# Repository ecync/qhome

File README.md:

# QHome Automation System

## 🏠 Project Overview
**QHome** is a comprehensive, full-stack IoT Smart Home solution designed to provide real-time monitoring, automation, and remote control of environmental and power sensors. The system is built on a modular architecture, spanning from custom PCB hardware design to a modern web-based dashboard.

This project integrates embedded systems connectivity (ESP32/ESP8266), robust backend services (NestJS/MQTT), and an interactive frontend (React) to create a seamless smart home experience.

## 🏗️ System Architecture

The system operates on a publish-subscribe model using MQTT for low-latency communication between the hardware nodes and the server.

```mermaid
graph LR
    subgraph Hardware Layer
        Node[ESP32 QHome Node]
        Sensors[Sensors: DHT, MQ, ACS, ZMPT]
        Relays[Relays & Actuators]
        Node --- Sensors
        Node --- Relays
    end

    subgraph Communication
        MQTT[MQTT Broker]
        WiFi[WiFi Network]
        Node -.->|MQTT/WS| WiFi
        WiFi -.-> MQTT
    end

    subgraph Cloud/Server Layer
        Backend[NestJS Backend]
        DB[(MongoDB)]
        Backend <-->|Pub/Sub| MQTT
        Backend <-->|Data Persistence| DB
    end

    subgraph User Interface
        Frontend[React Dashboard]
        User((User))
        User --> Frontend
        Frontend <-->|HTTP/REST| Backend
        Frontend <-->|Socket.io| Backend
    end
```

## 📊 Data Flow Diagram

This diagram illustrates how data moves through the entire system, from sensor acquisition to user visualization.

```mermaid
flowchart TB
    subgraph IoT_Node["IoT Node Layer"]
        Sensors[Physical Sensors<br/>DHT, MQ, ACS, ZMPT, PIR, LDR]
        ADC[Analog-to-Digital<br/>Conversion]
        Process[Data Processing<br/>& Aggregation]
        JSON[JSON Payload<br/>Generation]
        
        Sensors -->|Analog/Digital| ADC
        ADC -->|Raw Values| Process
        Process -->|Structured Data| JSON
    end
    
    subgraph Communication_Layer["Communication Layer"]
        WiFi[WiFi Module]
        MQTT_Pub[MQTT Publisher<br/>Topic: node/send]
        MQTT_Broker[MQTT Broker<br/>158.101.98.79:9001]
        MQTT_Sub[MQTT Subscriber<br/>Topic: node/cmd]
        
        JSON -->|Transmit| WiFi
        WiFi -->|Publish| MQTT_Pub
        MQTT_Pub -->|WebSocket| MQTT_Broker
        MQTT_Broker -->|Commands| MQTT_Sub
        MQTT_Sub -->|Receive| WiFi
    end
    
    subgraph Backend_Layer["Backend Service Layer"]
        Gateway[MQTT Gateway<br/>Service]
        Validator[Data Validator<br/>& Parser]
        EventEmitter[Event Emitter]
        DB_Write[Database Writer]
        Socket_Emit[Socket.IO Emitter]
        MongoDB[(MongoDB<br/>Collections)]
        API[REST API<br/>Controllers]
        
        MQTT_Broker -->|Subscribed Data| Gateway
        Gateway -->|Validate| Validator
        Validator -->|Emit Events| EventEmitter
        EventEmitter -->|Store| DB_Write
        EventEmitter -->|Broadcast| Socket_Emit
        DB_Write -->|Persist| MongoDB
        API -->|Query| MongoDB
    end
    
    subgraph Frontend_Layer["Frontend Application Layer"]
        Socket_Client[Socket.IO Client]
        State[React State<br/>Management]
        UI_Dashboard[Dashboard UI<br/>Components]
        UI_Analytics[Analytics UI<br/>Charts]
        HTTP_Client[HTTP Client<br/>API Service]
        
        Socket_Emit -.->|Real-time Push| Socket_Client
        Socket_Client -->|Update| State
        HTTP_Client -->|Fetch Historical| API
        API -->|Response| HTTP_Client
        HTTP_Client -->|Update| State
        State -->|Render| UI_Dashboard
        State -->|Render| UI_Analytics
    end
    
    subgraph User_Layer["User Interaction"]
        User((User))
        Browser[Web Browser]
        
        User -->|View/Control| Browser
        Browser <-->|Display| UI_Dashboard
        Browser <-->|Display| UI_Analytics
        Browser -->|Commands| HTTP_Client
    end
    
    HTTP_Client -.->|Control Commands| API
    API -.->|Publish to node/cmd| MQTT_Broker
    
    style IoT_Node fill:#e1f5ff
    style Communication_Layer fill:#fff3e0
    style Backend_Layer fill:#f3e5f5
    style Frontend_Layer fill:#e8f5e9
    style User_Layer fill:#fce4ec
```

### Data Flow Description

**1. Sensor Data Acquisition (IoT Node)**
- Physical sensors continuously monitor environmental and power parameters
- Analog sensors output voltage levels converted to digital values via ADC
- Data is processed, calibrated, and packaged into JSON format

**2. Data Transmission (Communication Layer)**
- JSON payload transmitted over WiFi to MQTT broker
- Published to `node/send` topic via WebSocket protocol
- Bidirectional communication allows receiving commands on `node/cmd` topic

**3. Data Processing (Backend Service)**
- MQTT Gateway subscribes to node data streams
- Incoming data is validated and parsed
- Event system triggers parallel operations:
  - Persistent storage in MongoDB collections
  - Real-time broadcast to connected frontend clients via Socket.IO

**4. Data Presentation (Frontend Application)**
- Socket.IO client receives real-time updates for live dashboard
- HTTP client fetches historical data for analytics and trends
- React state management updates UI components reactively

**5. User Control Loop**
- User interactions trigger API calls to backend
- Backend publishes control commands to MQTT broker
- IoT node receives and executes commands (relay control, configuration updates)

## 🔄 Software Flow Diagram

This diagram shows the complete software execution flow from system startup to continuous operation.

```mermaid
flowchart TD
    Start([System Power On]) --> Init_Check{Component<br/>Ready?}
    
    Init_Check -->|Hardware| Init_Hardware[Initialize Hardware<br/>• GPIO Pins<br/>• LCD Display<br/>• Sensors<br/>• Relays]
    Init_Check -->|Backend| Init_Backend[Initialize Backend<br/>• Load Config<br/>• Connect MongoDB<br/>• Start HTTP Server]
    Init_Check -->|Frontend| Init_Frontend[Initialize Frontend<br/>• Load React App<br/>• Check Session<br/>• Setup Routes]
    
    Init_Hardware --> Check_Config{Config<br/>Exists?}
    Check_Config -->|No| AP_Mode[Start WiFi AP Mode<br/>Show Config Portal]
    AP_Mode --> Wait_Config[Wait for User<br/>to Configure WiFi]
    Wait_Config -->|Configured| Save_Config[Save to EEPROM]
    Save_Config --> Connect_WiFi
    
    Check_Config -->|Yes| Connect_WiFi[Connect to WiFi]
    Connect_WiFi --> WiFi_Success{Connected?}
    WiFi_Success -->|No| AP_Mode
    WiFi_Success -->|Yes| Connect_MQTT[Connect to<br/>MQTT Broker]
    
    Connect_MQTT --> MQTT_Success{Connected?}
    MQTT_Success -->|No| Retry_MQTT[Retry Connection<br/>Exponential Backoff]
    Retry_MQTT --> MQTT_Success
    MQTT_Success -->|Yes| Subscribe_Topics[Subscribe to<br/>node/cmd Topic]
    
    Init_Backend --> Connect_DB[Connect to MongoDB]
    Connect_DB --> DB_Success{Connected?}
    DB_Success -->|No| Error_Exit[Log Error & Exit]
    DB_Success -->|Yes| Connect_MQTT_Backend[Connect to<br/>MQTT Broker as Client]
    Connect_MQTT_Backend --> Backend_Subscribe[Subscribe to<br/>node/send Topic]
    Backend_Subscribe --> Start_API[Start REST API<br/>& Socket.IO Server]
    
    Init_Frontend --> Check_Auth{User<br/>Authenticated?}
    Check_Auth -->|No| Show_Login[Show Login Page]
    Show_Login --> User_Login[User Enters<br/>Credentials]
    User_Login --> Validate_Auth[Validate Against<br/>Backend API]
    Validate_Auth --> Auth_Valid{Valid?}
    Auth_Valid -->|No| Show_Login
    Auth_Valid -->|Yes| Store_Session[Store Session<br/>in SessionStorage]
    
    Check_Auth -->|Yes| Load_Dashboard
    Store_Session --> Load_Dashboard[Load Dashboard<br/>Components]
    Load_Dashboard --> Connect_Socket[Connect Socket.IO<br/>to Backend]
    
    Subscribe_Topics --> Ready_Node[Node Ready<br/>Play Beep Sound]
    Start_API --> Ready_Backend[Backend Ready<br/>Log Status]
    Connect_Socket --> Ready_Frontend[Frontend Ready<br/>Display Dashboard]
    
    Ready_Node --> Main_Loop_Node[Main Loop: Node]
    Ready_Backend --> Main_Loop_Backend[Main Loop: Backend]
    Ready_Frontend --> Main_Loop_Frontend[Main Loop: Frontend]
    
    Main_Loop_Node --> Read_Sensors[Read All Sensors<br/>Every Interval]
    Read_Sensors --> Process_Data[Process & Calculate<br/>• Temperature/Humidity<br/>• Gas Level<br/>• Power/Energy<br/>• Motion/Light]
    Process_Data --> Check_Thresholds{Thresholds<br/>Exceeded?}
    Check_Thresholds -->|Yes| Trigger_Alert[Trigger Local Alert<br/>• Activate Buzzer<br/>• Update LCD<br/>• Send MQTT Alert]
    Check_Thresholds -->|No| Check_Sync
    Trigger_Alert --> Check_Sync
    
    Check_Sync{Time to<br/>Sync?} -->|Yes| Publish_Data[Publish JSON<br/>to node/send]
    Check_Sync -->|No| Update_Display
    Publish_Data --> Update_Display[Update LCD<br/>Display Status]
    
    Update_Display --> Listen_Commands[Listen for<br/>MQTT Commands]
    Listen_Commands --> Command_Received{Command?}
    Command_Received -->|Yes| Execute_Command[Execute Command<br/>• Toggle Relay<br/>• Update Config<br/>• Restart]
    Command_Received -->|No| Main_Loop_Node
    Execute_Command --> Main_Loop_Node
    
    Main_Loop_Backend --> Listen_MQTT[Listen for<br/>MQTT Messages]
    Listen_MQTT --> MQTT_Message{Message<br/>Received?}
    MQTT_Message -->|Yes| Parse_Message[Parse Message Type<br/>• _sensor_data<br/>• _alert<br/>• _error<br/>• _ack]
    MQTT_Message -->|No| Handle_HTTP
    
    Parse_Message --> Save_DB[Save to MongoDB<br/>Appropriate Collection]
    Save_DB --> Emit_Socket[Emit to Socket.IO<br/>Connected Clients]
    Emit_Socket --> Handle_HTTP
    
    Handle_HTTP[Handle HTTP Requests<br/>• GET sensor-data<br/>• POST commands<br/>• POST config]
    Handle_HTTP --> API_Request{Request?}
    API_Request -->|GET| Query_DB[Query MongoDB<br/>Return Results]
    API_Request -->|POST| Publish_Command[Publish to<br/>node/cmd Topic]
    API_Request -->|None| Main_Loop_Backend
    Query_DB --> Main_Loop_Backend
    Publish_Command --> Main_Loop_Backend
    
    Main_Loop_Frontend --> Socket_Listen[Listen for<br/>Socket.IO Events]
    Socket_Listen --> Socket_Event{Event<br/>Received?}
    Socket_Event -->|Yes| Update_State[Update React State<br/>Trigger Re-render]
    Socket_Event -->|No| User_Action
    Update_State --> User_Action
    
    User_Action{User<br/>Action?}
    User_Action -->|View Analytics| Fetch_History[Fetch Historical<br/>Data via API]
    User_Action -->|Send Command| Send_Command[Send POST Request<br/>to Backend API]
    User_Action -->|Update Settings| Send_Config[Send Config Update<br/>to Backend API]
    User_Action -->|None| Main_Loop_Frontend
    
    Fetch_History --> Render_Charts[Render Charts<br/>with Recharts]
    Render_Charts --> Main_Loop_Frontend
    Send_Command --> Main_Loop_Frontend
    Send_Config --> Main_Loop_Frontend
    
    style Init_Hardware fill:#e1f5ff
    style Init_Backend fill:#f3e5f5
    style Init_Frontend fill:#e8f5e9
    style Main_Loop_Node fill:#ffebee
    style Main_Loop_Backend fill:#fff3e0
    style Main_Loop_Frontend fill:#e0f2f1
```

## 📂 Project Modules

The repository is organized into four main operational layers. Click on the module links for detailed documentation, installation steps, and API references.

| Module | Directory | Description | Technology |
| :--- | :--- | :--- | :--- |
| **Hardware Design** | [**`/pcb`**](pcb/README.md) | Custom PCB layouts, schematics, and BOM. | Eagle CAD / Fusion 360 |
| **Firmware** | [**`/node`**](node/README.md) | C++ firmware for ESP controllers implementing sensor logic. | Arduino / C++ |
| **Backend API** | [**`/backend`**](backend/README.md) | Server logic, database management, and MQTT processing. | NestJS, MongoDB, TypeScript |
| **Frontend UI** | [**`/frontend`**](frontend/README.md) | Web dashboard for monitoring and control. | React, Vite, Tailwind CSS |

## ✨ Key Features

*   **Real-time Monitoring**: Live streaming of Temperature, Humidity, Air Quality (Gas), and Ambient Light levels.
*   **Energy Management**: Precise AC Voltage, Current, Power (W), and Energy (kWh) metering using ZMPT101B and ACS712 sensors.
*   **Safety & Alerts**: Instant automated alerts for gas leaks, fire detection, or abnormal power usage via Buzzer and MQTT push notifications.
*   **Remote Control**: Toggle lights and appliances remotely via the web dashboard.
*   **Data Analytics**: Historical charts and graphs to track power consumption and environmental trends over time.
*   **Secure Access**: Token-based authentication (Custom Headers) ensuring only authorized users can control the system.

## 🚀 Getting Started

To spin up the entire system locally, follow the **Installation & Setup** guides in each module's README. A high-level startup order is recommended:

1.  **Infrastructure**: Ensure you have a MongoDB instance and an MQTT Broker (e.g., Mosquitto) running.
2.  **Backend**: Start the [Backend Service](backend/README.md) to initialize the API and Database connections.
3.  **Frontend**: Launch the [Web Dashboard](frontend/README.md) to interact with the system.
4.  **Hardware**: Flash the [Firmware](node/README.md) to your ESP32/ESP8266 device and configure it to connect to your Wi-Fi and MQTT Broker.

## 🛠️ Technology Stack

*   **Hardware**: ESP32, ESP8266, DHT11/22, MQ-135, ACS712, ZMPT101B, Relay Modules.
*   **Protocol**: MQTT (Message Queuing Telemetry Transport) over WebSockets.
*   **Server**: Node.js, NestJS, Mongoose.
*   **Database**: MongoDB (NoSQL).
*   **Client**: React.js, TypeScript, Tailwind CSS, Recharts.

---
*Developed by Eshan Chathuranga*

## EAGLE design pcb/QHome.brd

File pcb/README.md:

# PCB Design - QHome Automation System

## Overview
This directory contains the Eagle CAD design files for the **QHome** main controller board. This PCB is the hardware backbone of the Home Automation System, designed to integrate the microcontroller with various environmental sensors, power monitoring modules, and communication interfaces.

## Project Structure
- **[QHome.sch](QHome.sch)**: The schematic design file detailing the circuit logic and connections.
- **[QHome.brd](QHome.brd)**: The printed circuit board layout file used for fabrication.
- **[QHome.dru](QHome.dru)**: The Design Rule Check (DRC) file defining manufacturing constraints.

## Visuals

### Schematic Diagram

### PCB Layout (Trace View)

### Component View (3D/Assembly)

## Hardware Specifications

### Supported Microcontroller
The board is designed to host an ESP-based microcontroller (e.g., ESP8266 NodeMCU or ESP32), handling Wi-Fi connectivity and MQTT communication.

### Sensor & Peripheral Interfaces
Based on the firmware modules, this PCB includes interfaces for:

1.  **Power Monitoring**:
    *   **Voltage**: Interface for ZMPT101B AC voltage sensor.
    *   **Current**: Interface for ACS712 current sensor.
2.  **Environmental Monitoring**:
    *   **Climate**: Header for DHT11/DHT22 (Temperature & Humidity).
    *   **Air Quality**: Heading for MQ-series gas sensors (e.g., MQ-2, MQ-135).
    *   **Light**: Analog input for Light Dependent Resistor (LDR).
    *   **Presence**: Input for PIR Motion Sensor.
3.  **User Interface**:
    *   **Display**: I2C header for 16x2 or 20x4 Liquid Crystal Display (LCD).

## Fabrication Details
*   **Layers**: 2-Layer (Top & Bottom Signal/Polygon pours).
*   **Material**: Standard FR-4.
*   **Mask**: Green (or preferred color).
*   **Silkscreen**: Top side for component placement guides.

## Assembly Instructions
1.  **PCB Manufacturing**: Export Gerber files from `QHome.brd` or send the `.brd` file directly to a supported PCB fabrication house (e.g., OSH Park, PCBWay, JLCPCB).
2.  **Sourcing Components**: Generate a Bill of Materials (BOM) from `QHome.sch` inside Eagle CAD.
3.  **Soldering**:
    *   Start with low-profile components (resistors, diodes).
    *   Install headers and connectors (JST, Dupont, or screw terminals).
    *   Solder larger modules or sockets for the microcontroller and sensors.
4.  **Testing**: Before inserting the MCU, power the board and check voltage rails (5V, 3.3V) with a multimeter to facilitate safe operation.

## Design Tools
*   **Software**: Autodesk EAGLE (or compatible EDA software like Fusion 360 Electronics).

---

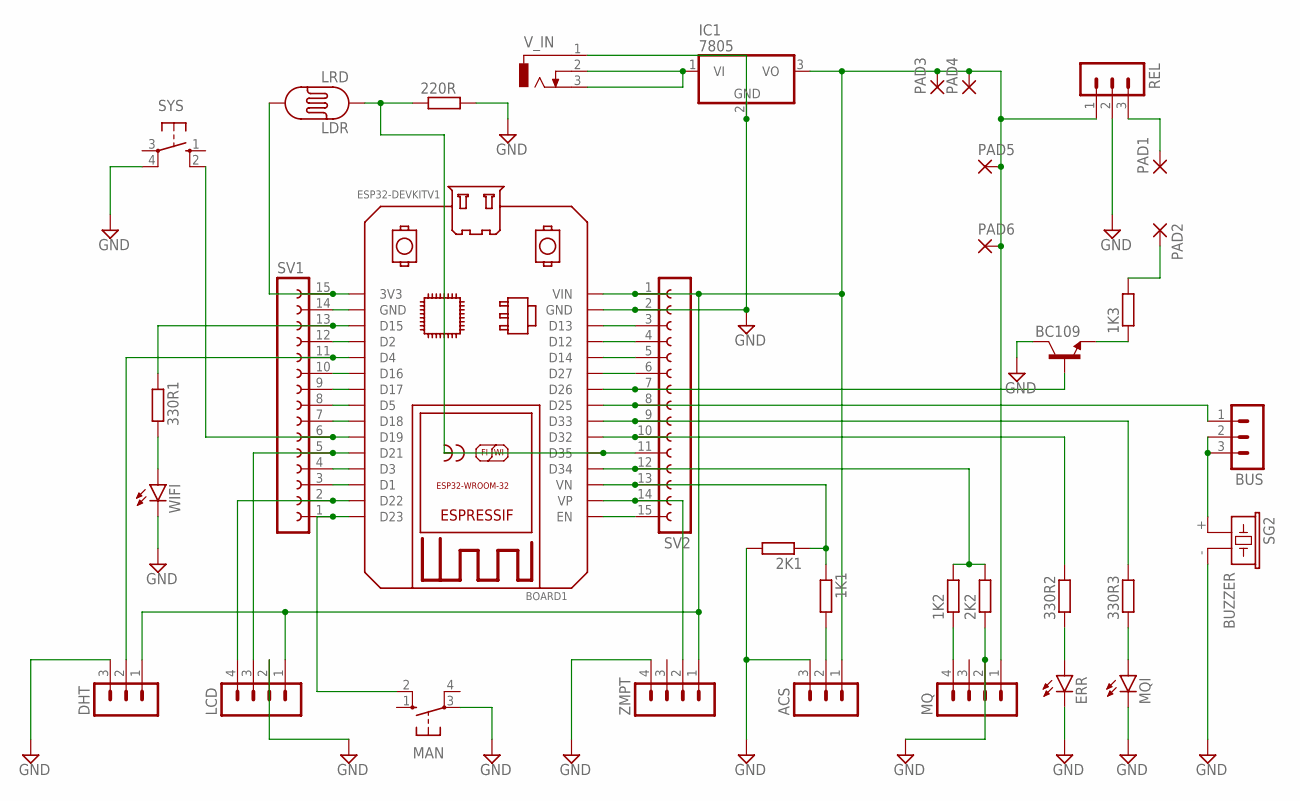
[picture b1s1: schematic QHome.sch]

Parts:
1K1, 1K2, 1K3, 2K1, 2K2, 220R, 330R1, 330R2, 330R3: R-EU_0207/7; 0207/7
ACS: MA03-1
BC109: BF422-NPN-TO92-BCE; TO92-BCE
BOARD1: ESP32DEVKITV1; ESP32-DEVKITV1
BUS: MA03-1
DHT: MA03-1
ERR: LED5MM
IC1: 7805; TO220V
LCD: MA04-1
LDR: LRD; ON_BOARD
MAN: 10-XX; B3F-10XX
MQ: MA04-1
MQI: LED5MM
PAD1, PAD2, PAD3, PAD4, PAD5, PAD6: 2,54/1,1
REL: MA03-1
SG2: BUZZER; F/CM12P
SV1, SV2: FE15-1; FE15
SYS: 10-XX; B3F-10XX
V_IN: DCJ0303
WIFI: LED5MM
ZMPT: MA04-1

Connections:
GND: 2K1.2, 2K2.1, 220R.2, ACS.3, BC109.C, BOARD1.GND, DHT.3, ERR.K (C), IC1.2 (GND), LCD.2, MAN.3, MQ.2, MQI.K (C), REL.2, SG2.- (2), SV2.2, SYS.4 (P1), V_IN.1, WIFI.K (C), ZMPT.4
unnamed: IC1.1 (VI), V_IN.2, V_IN.3
unnamed: BOARD1.VP, SV2.14, ZMPT.2
unnamed: BOARD1.3V3, LDR.2, SV1.15
unnamed: 1K1.1, 2K1.1, BOARD1.VN, SV2.13
unnamed: 1K1.2, ACS.2
unnamed: 1K2.1, MQ.4
unnamed: ACS.1, BOARD1.VIN, DHT.1, IC1.3 (VO), LCD.1, MQ.1, PAD3.1, PAD4.1, PAD5.1, PAD6.1, REL.1, SV2.1, ZMPT.1
unnamed: 1K2.2, 2K2.2, BOARD1.D34, SV2.12
unnamed: 220R.1, BOARD1.D35, LDR.1, SV2.11
unnamed: BOARD1.D21, LCD.3, SV1.5
unnamed: BOARD1.D22, LCD.4, SV1.2
unnamed: 330R1.2, WIFI.A
unnamed: BOARD1.D4, DHT.2, SV1.11
unnamed: 330R2.1, ERR.A
unnamed: 330R1.1, BOARD1.D15, SV1.13
unnamed: 330R3.2, BOARD1.D33, SV2.9
unnamed: 330R3.1, MQI.A
unnamed: 330R2.2, BOARD1.D32, SV2.10
unnamed: BOARD1.D25, BUS.1, SV2.8
unnamed: BUS.2, BUS.3, SG2.+ (1)
unnamed: 1K3.2, PAD2.1
unnamed: BOARD1.D19, SV1.6, SYS.2 (S1)
unnamed: BOARD1.D23, MAN.2 (S1), SV1.1
unnamed: BOARD1.D1, SV1.3
unnamed: BOARD1.D3, SV1.4
unnamed: BOARD1.D18, SV1.7
unnamed: BOARD1.D5, SV1.8
unnamed: BOARD1.D17, SV1.9
unnamed: BOARD1.D16, SV1.10
unnamed: BOARD1.D2, SV1.12
unnamed: BOARD1.GND@1 (GND), SV1.14
unnamed: BOARD1.D13, SV2.3
unnamed: BOARD1.D12, SV2.4
unnamed: BOARD1.D14, SV2.5
unnamed: BOARD1.D27, SV2.6
unnamed: BOARD1.EN, SV2.15
unnamed: BC109.B, BOARD1.D26, SV2.7
unnamed: PAD1.1, REL.3
unnamed: 1K3.1, BC109.E

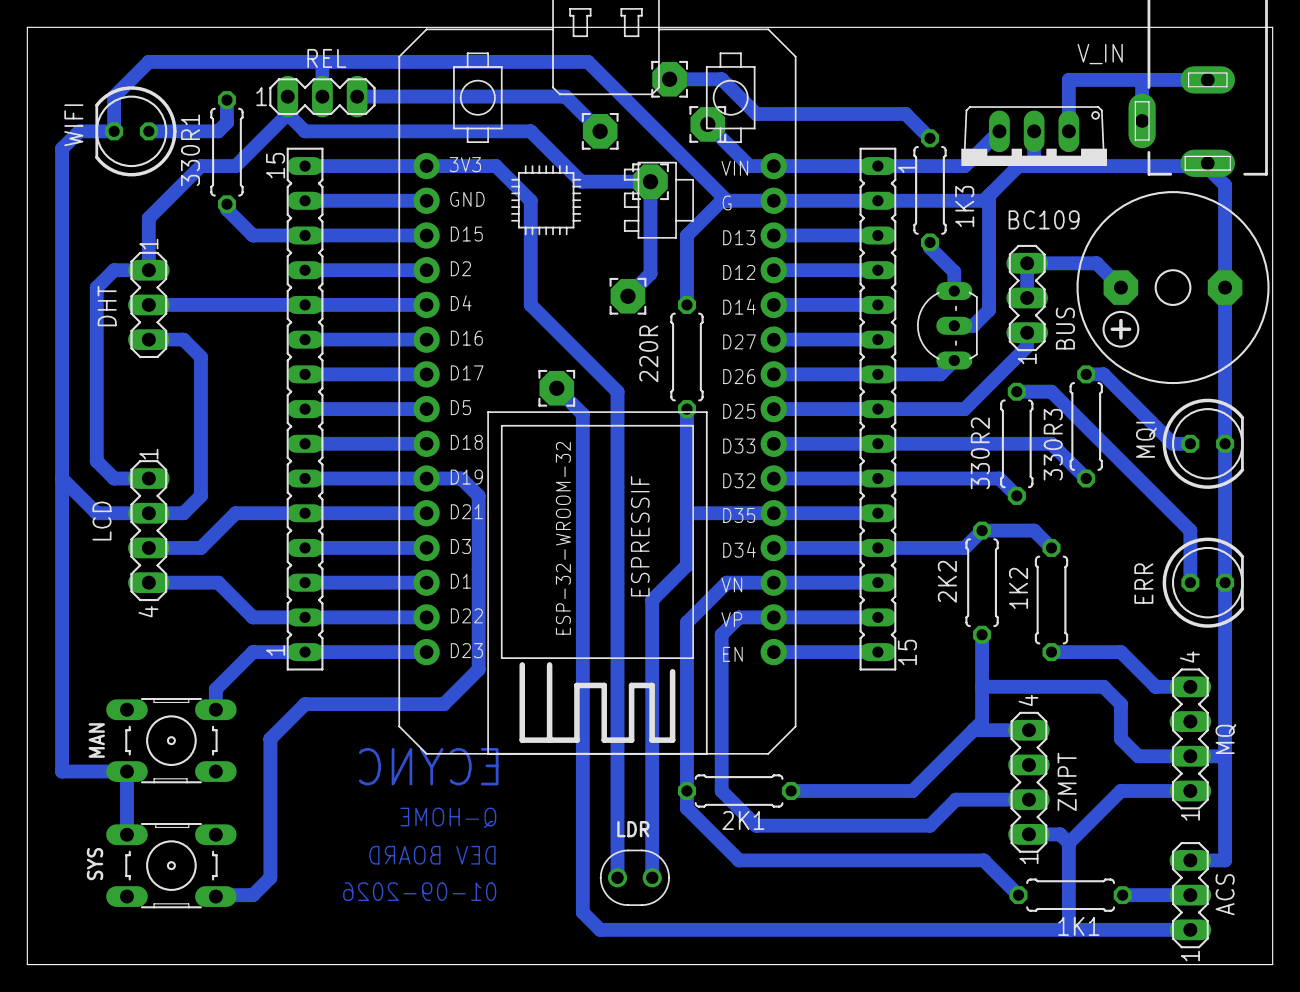
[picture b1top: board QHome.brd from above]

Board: 2 copper layers, 91.1 x 68.6 mm, 35 parts (0 on the bottom side), 40 nets.

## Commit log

2026-01-15 Add comprehensive diagrams and flow descriptions for data and software processes
    - Introduced Data Flow Diagram in README.md detailing sensor data acquisition, processing, and user interaction.
    - Added Software Flow Diagram illustrating system startup and continuous operation.
    - Included MQTT Message Flow Diagram in API.md to clarify message exchanges between components.
    - Enhanced backend processing documentation with a detailed Data Processing Flow diagram.
    - Updated frontend README.md with User Interaction Flow Diagram to depict user journeys and actions.
    - Revised node README.md to include Sensor Data Publishing Flow diagram outlining sensor data handling and MQTT publishing.
2026-01-15 Fix formatting of error and success messages in flowcharts in README files
2026-01-15 Fix Documentation diagram errors
